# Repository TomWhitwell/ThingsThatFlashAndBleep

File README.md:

# Things that Flash and Bleep

This is a bundle of documentation for an enrichment course in DIY electronics and music that I ran at [Dulwich Hamlet Junior School](http://www.dulwichhamletjuniorschool.org.uk/) in May/June 2015.  
The course was 4 x 90 minute sessions for 7-11 year olds, covering electronic music, building circuits on breadboards, and soldering together a Bleep-o-Matic (a modified [Atari Punk Console](https://en.wikipedia.org/wiki/Atari_Punk_Console)). 

### Contents 

- Hardware: Eagle PCB files, lasercut outlines and a BOM for the Bleep-o-Matic  
- Documentation: Powerpoint slides and printed materials 
- Next steps: some online resources and books for anyone wanting to learn more 
- Before starting, check the Issue Log for any unresolved problems
 
### History 

- The Rev2 PCB board designs (June 2015) in this repository fix a number of small issues on the boards used for the classes.  

#### License  
All hardware and documentation in this project is Creative Commons licensed by Tom Whitwell: [CC-BY-NC-SA: Attribution / ShareAlike / NonCommercial](https://creativecommons.org/licenses/by-nc-sa/4.0/)  
If you use any work in this project, you should credit me, and you must republish any changes you make under the same license. If you wish to use this commercially, you must [contact me](mailto:tom.whitwell@gmail.com) for permission and may have to pay a license fee.  
The core circuit was created as a Sound Synthesizer (then Stepped Tone Generator) by [Forrest Mims III](http://www.forrestmims.org/) in 1980, and renamed Atari Punk Console by [Kaustic Machines](http://compiler.kaustic.net/machines/apc.html) in 2005 or 2007.

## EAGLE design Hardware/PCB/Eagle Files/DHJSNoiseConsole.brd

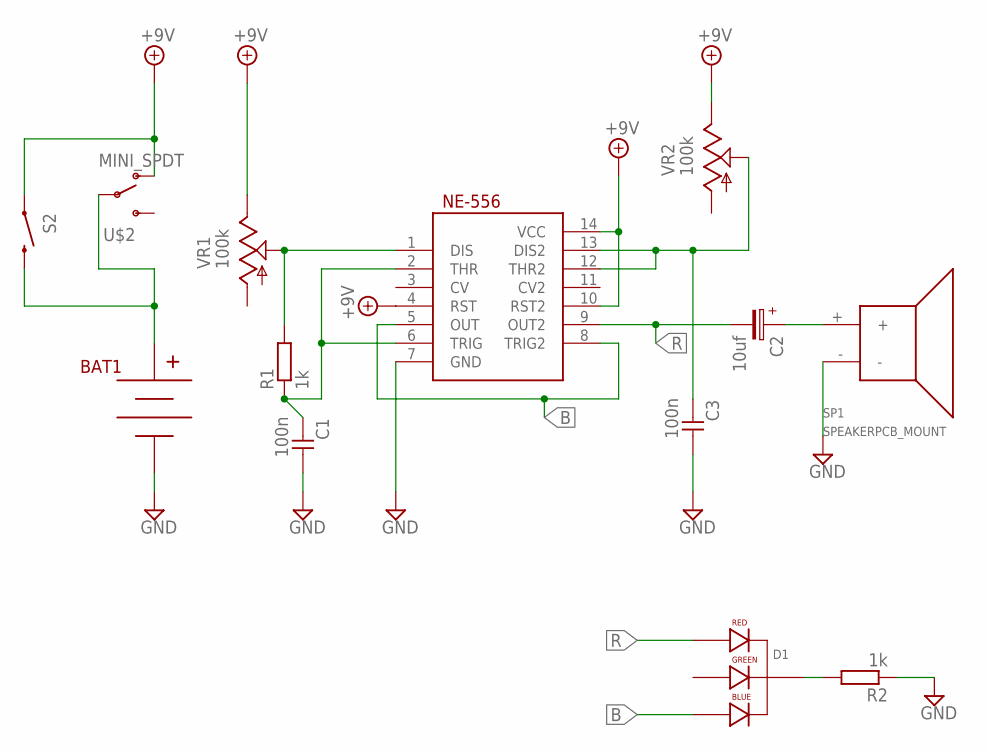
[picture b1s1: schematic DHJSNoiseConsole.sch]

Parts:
BAT1: BC9VPC
C1, C3: 100n; C050-024X044
C2: 10uf; 050_020
D1: LED-RGB-CC-THRUCLEAR; LED-RGB-THRU
NE-556: 556; DIL14
R1, R2: 1k; 10MM_RESISTOR
S2: SWITCH-MOMENTARY-2SIDE_EZ; TACTILE-PTH-SIDEEZ
SP1: SPEAKERPCB_MOUNT; PCB_MOUNT_SPEAKER
U$2: MINI_SPDT; MINI_SPDT_RIGHTANGLE
VR1, VR2: 100k; 9MM_SNAP-IN_POT

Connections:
+9V: NE-556.4 (RST), NE-556.10 (RST2), NE-556.14 (VCC), S2.1, U$2.UP (O), VR1.3 (E), VR2.3 (E)
B: D1.4 (BLUE_CATHODE), NE-556.5 (OUT), NE-556.8 (TRIG2)
GND: BAT1.V-, C1.1, C3.1, NE-556.7 (GND), R2.1, SP1.-
unnamed: NE-556.1 (DIS), R1.2, VR1.2 (S)
unnamed: BAT1.V+, S2.2, U$2.COMMON
unnamed: C3.2, NE-556.12 (THR2), NE-556.13 (DIS2), VR2.2 (S)
unnamed: D1.2 (CATHODE), R2.2
unnamed: C1.2, NE-556.2 (THR), NE-556.6 (TRIG), R1.1
unnamed: C2.+, SP1.+
R: C2.-, D1.1 (RED_CATHODE), NE-556.9 (OUT2)

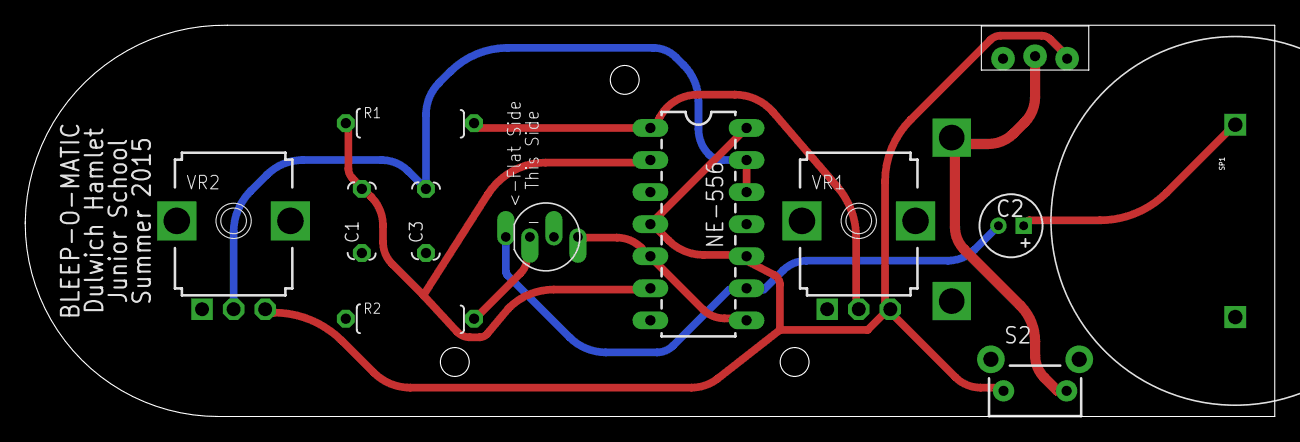
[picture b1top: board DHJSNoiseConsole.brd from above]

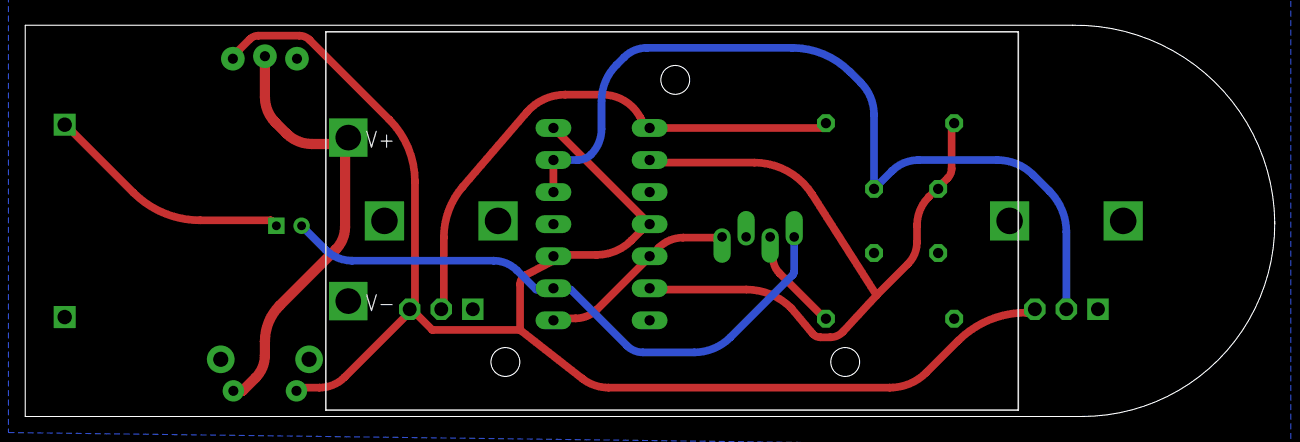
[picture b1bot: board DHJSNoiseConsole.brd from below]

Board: 4 copper layers, 99.0 x 31.0 mm, 14 parts (2 on the bottom side), 10 nets.

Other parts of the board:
U$1: MTM_1CM_KEEPOUT

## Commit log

2015-04-18 first design
2015-04-23 board
2015-04-27 finalised board
2015-04-27 gerbers
2015-06-05 Documentation
2015-06-14 folder changes
2015-06-14 panel upload
2015-06-14 reorganising folders
2015-06-14 PCB Eagle file revision fixes #1, fixes #2, fixes #3, fixes #4
2015-06-14 Rev 2 PCB uploads
2015-06-18 Writing the handout
2015-06-18 edits
2015-06-23 Handout edits

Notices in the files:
parts and their libraries:
SparkFun-AnalogIC: Licensing: CC v3.0 Share-Alike You are welcome to use this library for commercial purposes.
